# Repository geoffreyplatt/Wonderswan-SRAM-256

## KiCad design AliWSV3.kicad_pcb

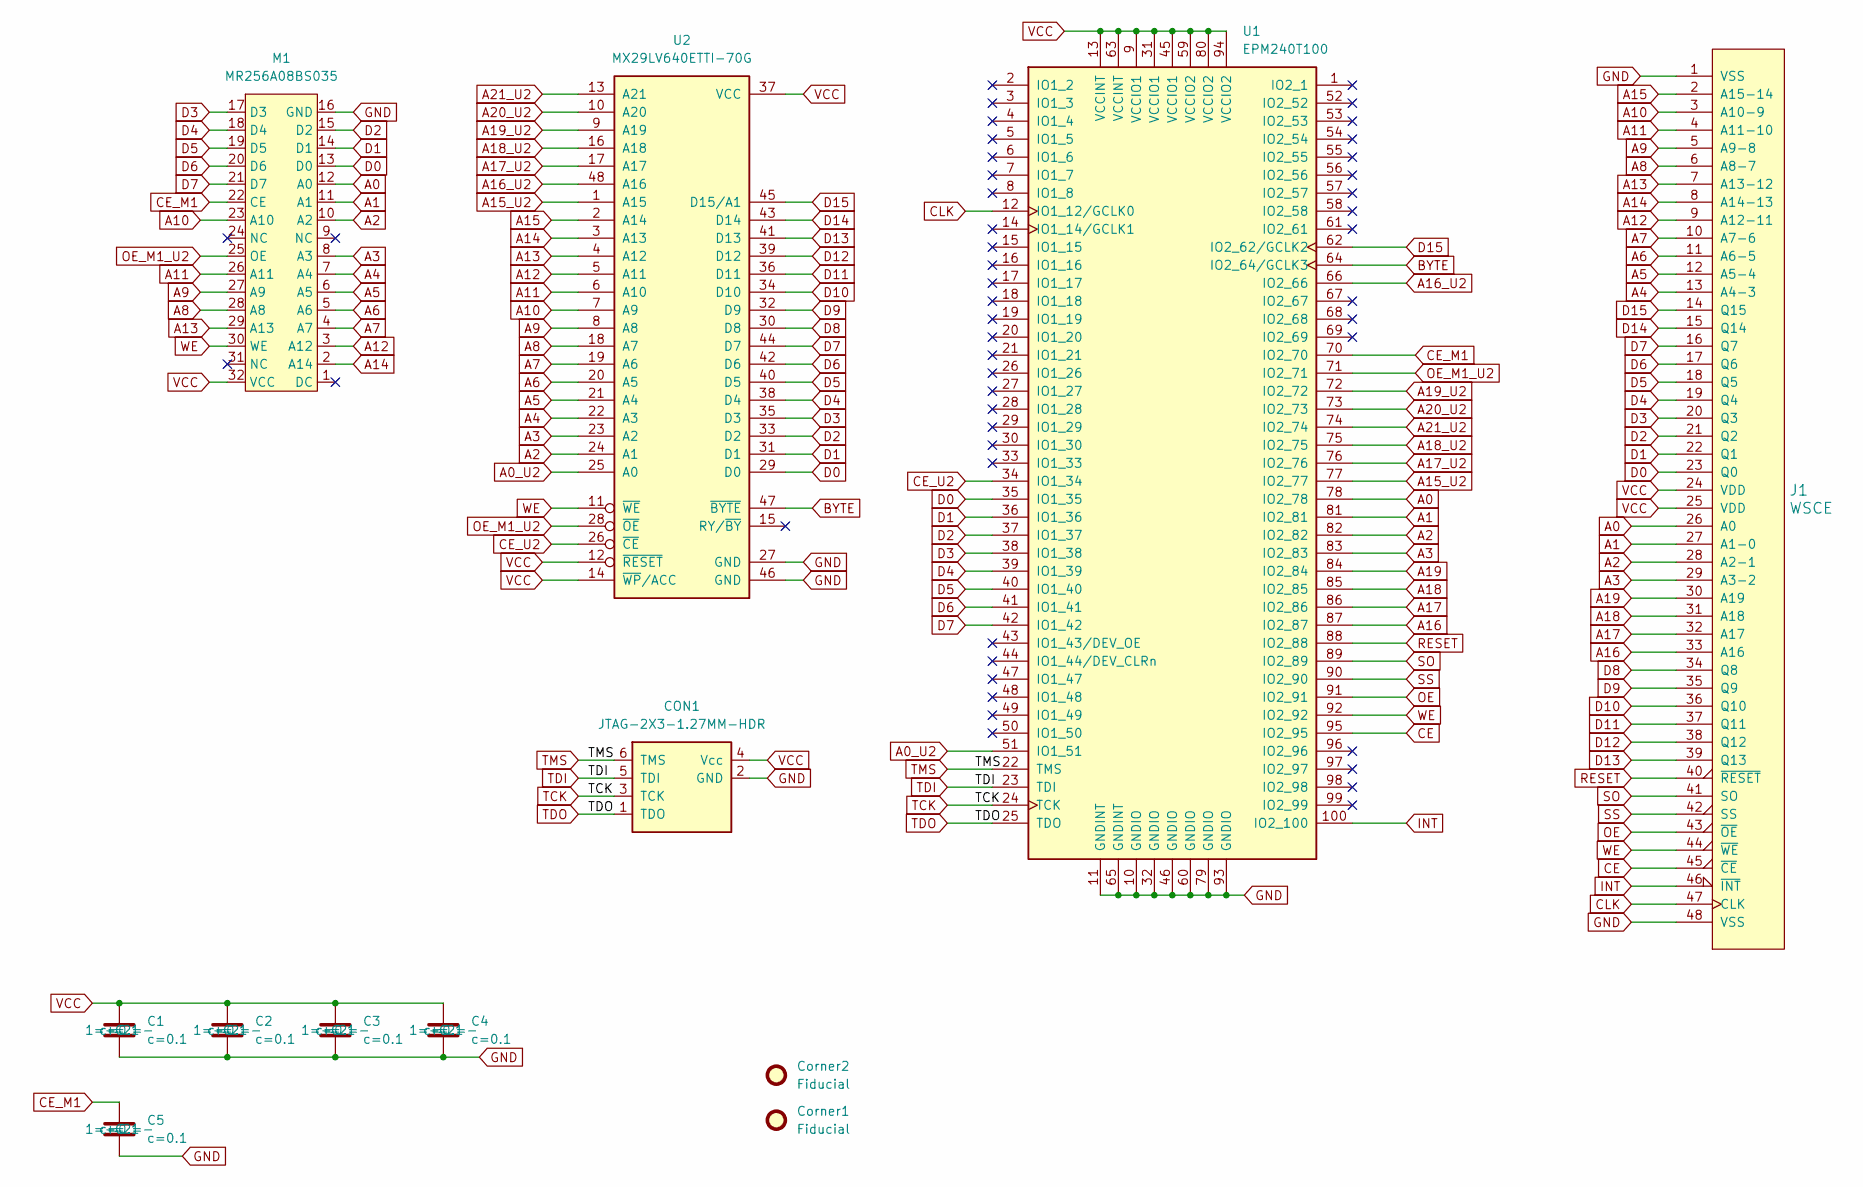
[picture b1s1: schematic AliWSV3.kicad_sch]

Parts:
C1, C2, C3, C4, C5: c=0.1; 0603; Digikey #ND
CON1: JTAG-2X3-1.27MM-HDR; PinHeader_2x03_P2.54mm_Vertical; Digikey 2057-HPH2-A-06-UA-ND
Corner1, Corner2: Fiducial; Fiducial_0.5mm_Mask1mm
J1: WSCE; EDGE
M1: MR256A08BS035; SOIC_32_7.5mmx20.5mm_P1.27
U1: EPM240T100; LQFP-100_14x14mm_P0.5mm
U2: MX29LV640ETTI-70G; TSSOP-48; Digikey 1092-1104-ND

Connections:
A0: J1.26 (A0), M1.12 (A0), U1.78 (IO2_78)
A0_U2: U1.51 (IO1_51), U2.25 (A0)
A1: J1.27 (A1-0), M1.11 (A1), U1.81 (IO2_81)
A2: J1.28 (A2-1), M1.10 (A2), U1.82 (IO2_82), U2.24 (A1)
A3: J1.29 (A3-2), M1.8 (A3), U1.83 (IO2_83), U2.23 (A2)
A4: J1.13 (A4-3), M1.7 (A4), U2.22 (A3)
A5: J1.12 (A5-4), M1.6 (A5), U2.21 (A4)
A6: J1.11 (A6-5), M1.5 (A6), U2.20 (A5)
A7: J1.10 (A7-6), M1.4 (A7), U2.19 (A6)
A8: J1.6 (A8-7), M1.28 (A8), U2.18 (A7)
A9: J1.5 (A9-8), M1.27 (A9), U2.8 (A8)
A10: J1.3 (A10-9), M1.23 (A10), U2.7 (A9)
A11: J1.4 (A11-10), M1.26 (A11), U2.6 (A10)
A12: J1.9 (A12-11), M1.3 (A12), U2.5 (A11)
A13: J1.7 (A13-12), M1.29 (A13), U2.4 (A12)
A14: J1.8 (A14-13), M1.2 (A14), U2.3 (A13)
A15: J1.2 (A15-14), U2.2 (A14)
A15_U2: U1.77 (IO2_77), U2.1 (A15)
A16: J1.33 (A16), U1.87 (IO2_87)
A16_U2: U1.66 (IO2_66), U2.48 (A16)
A17: J1.32 (A17), U1.86 (IO2_86)
A17_U2: U1.76 (IO2_76), U2.17 (A17)
A18: J1.31 (A18), U1.85 (IO2_85)
A18_U2: U1.75 (IO2_75), U2.16 (A18)
A19: J1.30 (A19), U1.84 (IO2_84)
A19_U2: U1.72 (IO2_72), U2.9 (A19)
A20_U2: U1.73 (IO2_73), U2.10 (A20)
A21_U2: U1.74 (IO2_74), U2.13 (A21)
BYTE: U1.64 (IO2_64/GCLK3), U2.47 (~BYTE)
CE: J1.45 (~CE), U1.95 (IO2_95)
CE_M1: C5.1, M1.22 (CE), U1.70 (IO2_70)
CE_U2: U1.34 (IO1_34), U2.26 (~CE)
CLK: J1.47 (CLK), U1.12 (IO1_12/GCLK0)
D0: J1.23 (Q0), M1.13 (D0), U1.35 (IO1_35), U2.29 (D0)
D1: J1.22 (Q1), M1.14 (D1), U1.36 (IO1_36), U2.31 (D1)
D2: J1.21 (Q2), M1.15 (D2), U1.37 (IO1_37), U2.33 (D2)
D3: J1.20 (Q3), M1.17 (D3), U1.38 (IO1_38), U2.35 (D3)
D4: J1.19 (Q4), M1.18 (D4), U1.39 (IO1_39), U2.38 (D4)
D5: J1.18 (Q5), M1.19 (D5), U1.40 (IO1_40), U2.40 (D5)
D6: J1.17 (Q6), M1.20 (D6), U1.41 (IO1_41), U2.42 (D6)
D7: J1.16 (Q7), M1.21 (D7), U1.42 (IO1_42), U2.44 (D7)
D8: J1.34 (Q8), U2.30 (D8)
D9: J1.35 (Q9), U2.32 (D9)
D10: J1.36 (Q10), U2.34 (D10)
D11: J1.37 (Q11), U2.36 (D11)
D12: J1.38 (Q12), U2.39 (D12)
D13: J1.39 (Q13), U2.41 (D13)
D14: J1.15 (Q14), U2.43 (D14)
D15: J1.14 (Q15), U1.62 (IO2_62/GCLK2), U2.45 (D15/A1)
GND: C1.2, C2.2, C3.2, C4.2, C5.2, CON1.2 (GND), J1.1 (VSS), J1.48 (VSS), M1.16 (GND), U1.10 (GNDIO), U1.11 (GNDINT), U1.32 (GNDIO), U1.46 (GNDIO), U1.60 (GNDIO), U1.65 (GNDINT), U1.79 (GNDIO), U1.93 (GNDIO), U2.27 (GND), U2.46 (GND)
INT: J1.46 (~INT), U1.100 (IO2_100)
OE: J1.43 (~OE), U1.91 (IO2_91)
OE_M1_U2: M1.25 (OE), U1.71 (IO2_71), U2.28 (~OE)
RESET: J1.40 (~RESET), U1.88 (IO2_88)
SO: J1.41 (SO), U1.89 (IO2_89)
SS: J1.42 (SS), U1.90 (IO2_90)
TCK: CON1.3 (TCK), U1.24 (TCK)
TDI: CON1.5 (TDI), U1.23 (TDI)
TDO: CON1.1 (TDO), U1.25 (TDO)
TMS: CON1.6 (TMS), U1.22 (TMS)
VCC: C1.1, C2.1, C3.1, C4.1, CON1.4 (Vcc), J1.24 (VDD), J1.25 (VDD), M1.32 (VCC), U1.9 (VCCIO1), U1.13 (VCCINT), U1.31 (VCCIO1), U1.45 (VCCIO1), U1.59 (VCCIO2), U1.63 (VCCINT), U1.80 (VCCIO2), U1.94 (VCCIO2), U2.12 (~RESET), U2.14 (~WP/ACC), U2.37 (VCC)
WE: J1.44 (~WE), M1.30 (WE), U1.92 (IO2_92), U2.11 (~WE)

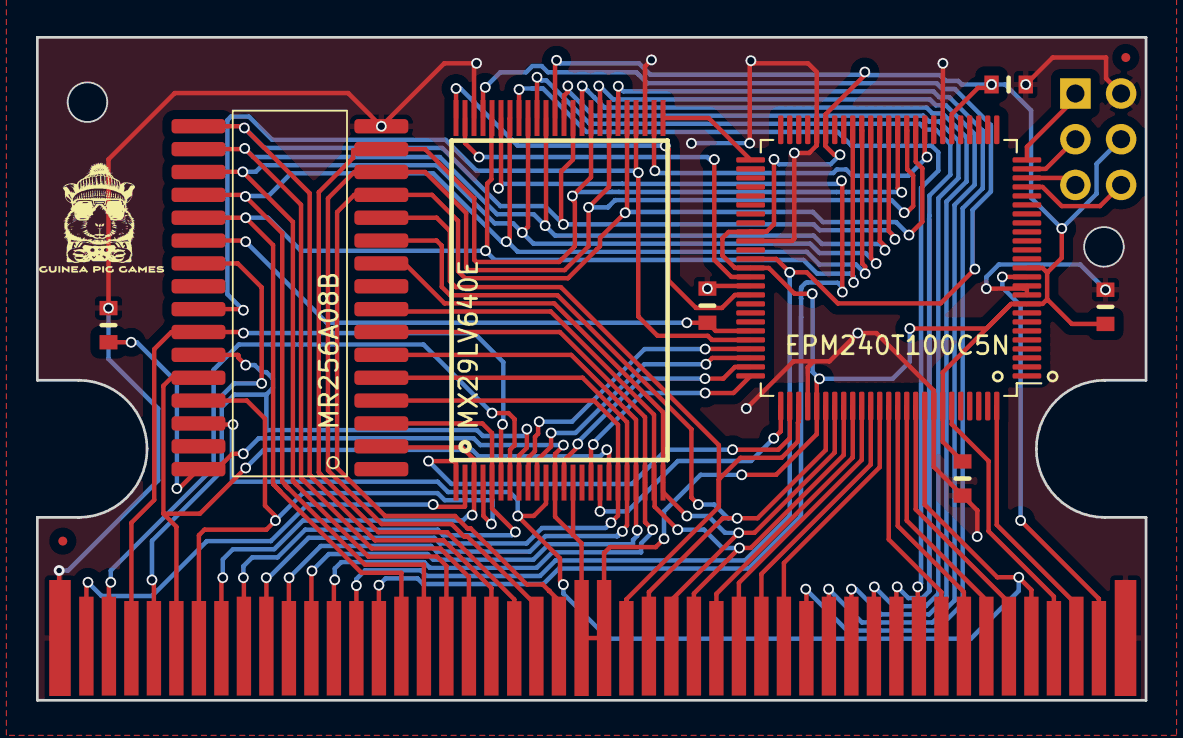
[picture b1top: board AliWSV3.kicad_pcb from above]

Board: 2 copper layers, 61.6 x 36.8 mm, 12 parts (0 on the bottom side), 62 nets.

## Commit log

2025-04-21 Added Gerbers and made some slight changes to PCB
